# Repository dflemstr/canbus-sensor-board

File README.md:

# canbus sensor board

A simple board optimized for handling I²C-connected sensors and communicate the status over CAN bus.

This repo contains both the PCB design files, and Rust-based firmware.

To flash and run the firmware:

  * Install Rust.  Using [rustup](https://rustup.rs/) is very strongly encouraged as it automates
    installation of cross compilation files and such.
  * Install `probe-rs`, a CLI for connecting to debug probes, with `cargo install probe-rs`.
  * Install `flip-link`, a meta-linker that puts the stack at the end of embedded memory, using
    `cargo install flip-link`.
  * Optionally update the `DEFAULT_CAN_ID` variable in `src/config.rs` if you want to change the CAN
    bus ID of the board without having to send it a command later.

Flash using a debug probe (easiest):

  * Connect the PCB to your computer using a SWD-based debug probe, for example a ST-Link v2 clone
    can be found super cheaply online, usually around $3 USD.  You can either solder wires to the
    provided pads (see PCB design files for pin assignments) or else use a TagConnect TC2030-NL
    cable, which has pogo pins matching the pads on the board, and can be bought with adapter wires
    that are compatible with an ST-Link module.
  * Run `cargo flash --release --chip STM32F103C8 --connect-under-reset` to flash to the board **or**
    run `cargo run` to flash the firmware using a debug build, start it, and stream debug logs to the
    terminal using the defmt RTT protocol. (You can of course also do any combination, e.g.
    `cargo run --release` etc)

Flash using CAN bus (more tricky perhaps):

  * Install [`can-prog`](https://github.com/marcinbor85/can-Prog), see the link for additional
    details.
  * Connect the PCB to a CAN bus.
  * Using some wires, first short the 3.3V and BOOT pads, and while still shorting the pads, also
    short the ~RST and GND pads.  This should put the board in DFU mode.
  * Build the firmware in release mode with `cargo build --release`
  * Convert the generated ELF file to a raw `.bin` file with:
    ```
    arm-none-eabi-objcopy -O binary target/thumbv7m-none-eabi/release/canbus-sensor-board image.bin
    ```

  * Run the command `canprog -f bin stm32 write image.bin -a 0x08000000` or similar. You might need
    to run `canprog stm32 erase` and such depending on the state of the firmware.

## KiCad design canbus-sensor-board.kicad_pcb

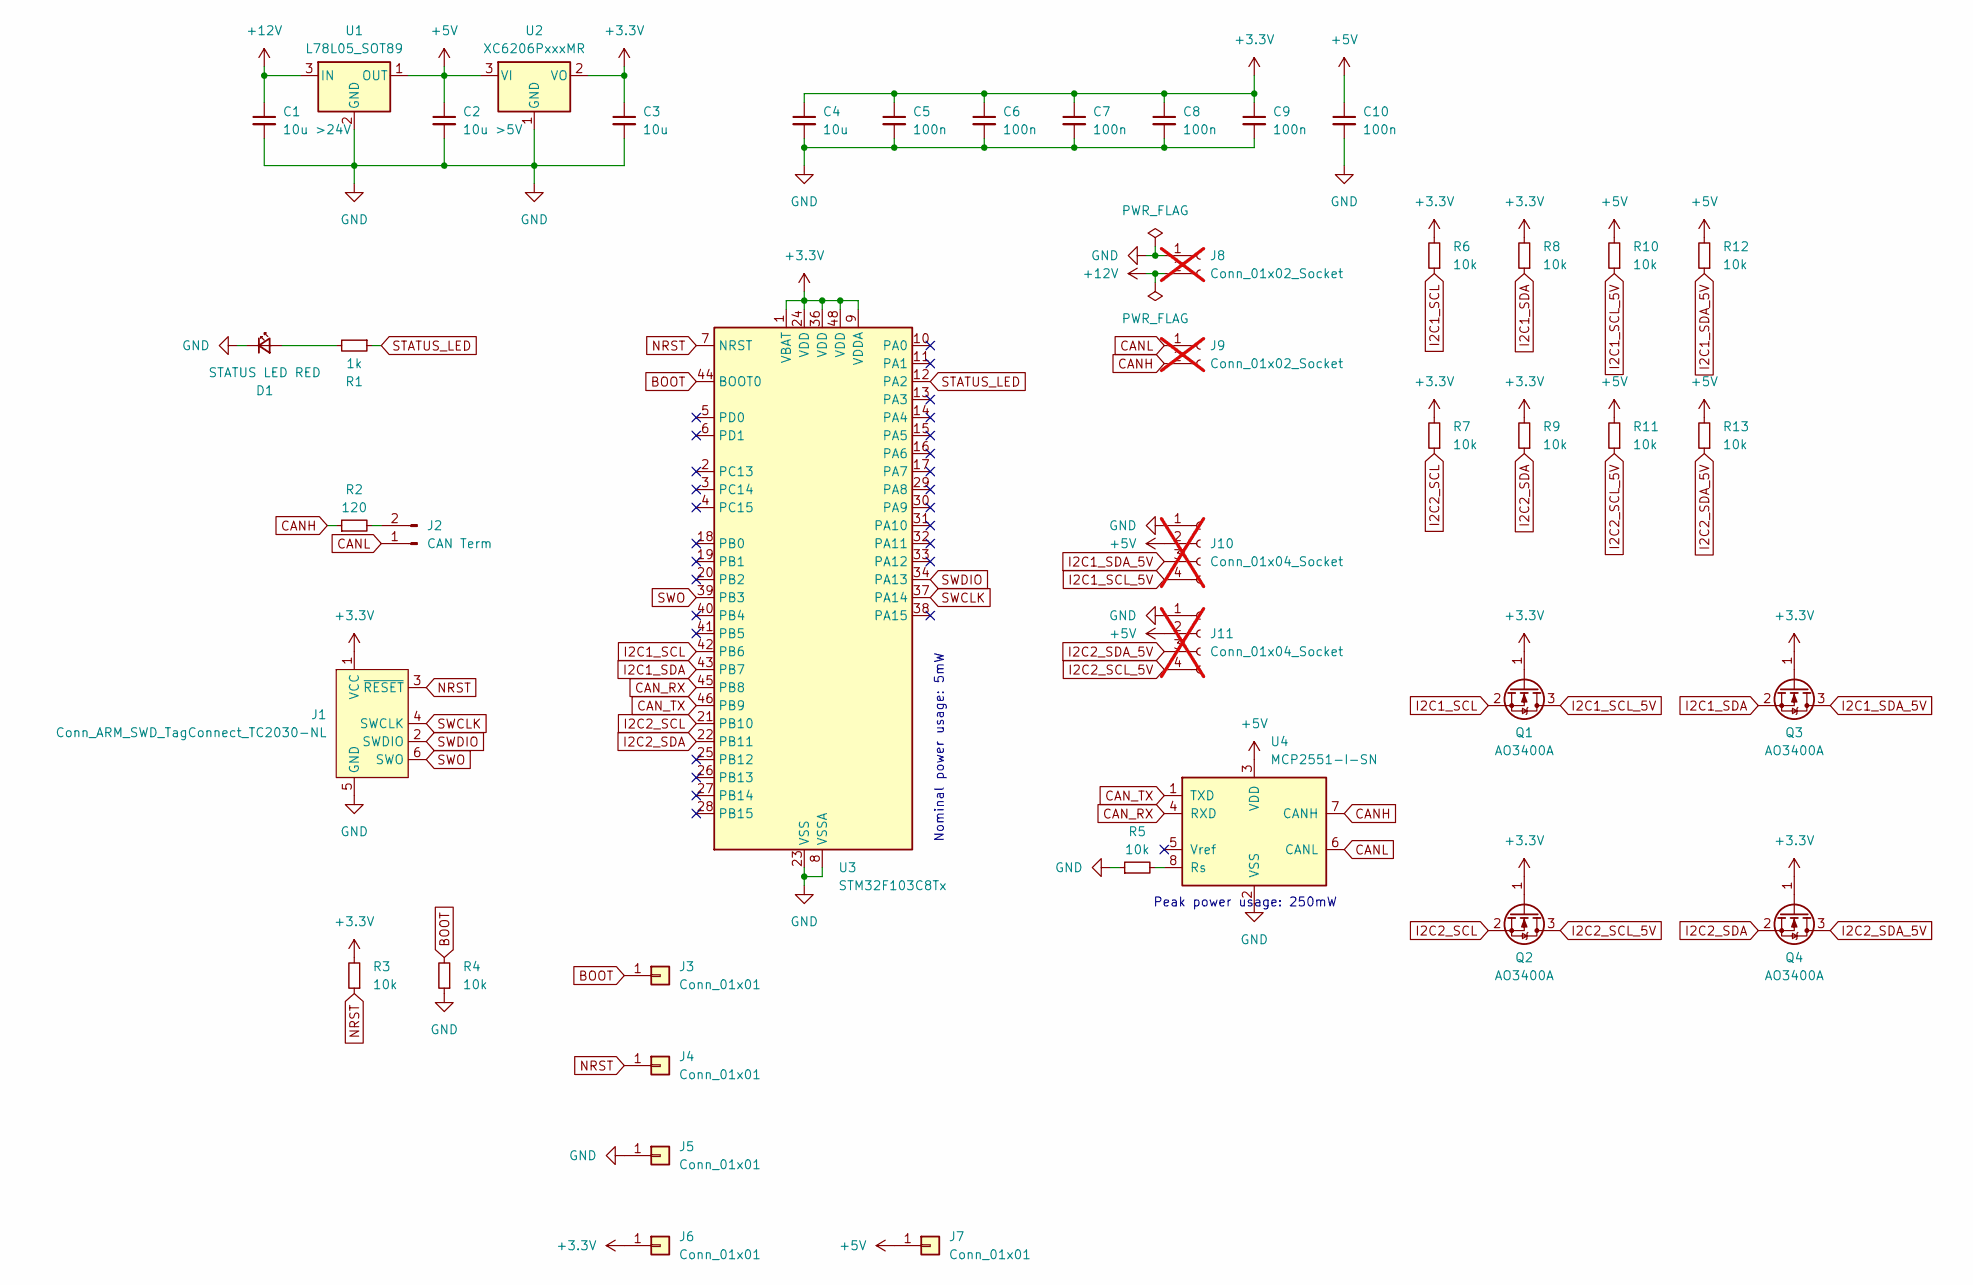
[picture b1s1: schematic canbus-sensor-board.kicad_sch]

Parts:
C1: 10u >24V; C_0805_2012Metric; MPN C440198
C2: 10u >5V; C_0603_1608Metric; MPN C19702
C3, C4: 10u; C_0402_1005Metric; MPN C15525
C5, C6, C7, C8, C9, C10: 100n; C_0402_1005Metric; MPN C1525
D1: STATUS LED RED; LED_0603_1608Metric; MPN C2286
J1: Conn_ARM_SWD_TagConnect_TC2030-NL; Tag-Connect_TC2030-IDC-NL_2x03_P1.27mm_Vertical
J2: CAN Term; SolderJumper-2_P1.3mm_Open_Pad1.0x1.5mm
J3, J4, J5, J6, J7: Conn_01x01; TestPoint_Pad_D1.0mm
J8, J9: Conn_01x02_Socket; PinHeader_1x02_P2.00mm_Vertical; not fitted
J10, J11: Conn_01x04_Socket; PinHeader_1x04_P2.00mm_Vertical; not fitted
Q1, Q2, Q3, Q4: AO3400A; SOT-23; MPN C20917
R1: 1k; R_0402_1005Metric; MPN C11702
R2: 120; R_0402_1005Metric; MPN C25079
R3, R4, R5, R6, R7, R8, R9, R10, R11, R12, R13: 10k; R_0402_1005Metric; MPN C25744
U1: L78L05_SOT89; SOT-89-3; MPN C71136
U2: XC6206PxxxMR; SOT-23-3; MPN C5446
U3: STM32F103C8Tx; LQFP-48_7x7mm_P0.5mm; MPN C8734
U4: MCP2551-I-SN; SOIC-8_3.9x4.9mm_P1.27mm; MPN C49558

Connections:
+3.3V: C3.1, C4.1, C5.1, C6.1, C7.1, C8.1, C9.1, J1.1 (VCC), J6.1, Q1.1 (G), Q2.1 (G), Q3.1 (G), Q4.1 (G), R3.2, R6.2, R7.2, R8.2, R9.2, U2.2 (VO), U3.1 (VBAT), U3.9 (VDDA), U3.24 (VDD), U3.36 (VDD), U3.48 (VDD)
+5V: C2.1, C10.1, J7.1, J10.2, J11.2, R10.2, R11.2, R12.2, R13.2, U1.1 (OUT), U2.3 (VI), U4.3 (VDD)
+12V: C1.1, J8.2, U1.3 (IN)
BOOT: J3.1, R4.2, U3.44 (BOOT0)
CANH: J9.2, R2.1, U4.7 (CANH)
CANL: J2.1, J9.1, U4.6 (CANL)
CAN_RX: U3.45 (PB8), U4.4 (RXD)
CAN_TX: U3.46 (PB9), U4.1 (TXD)
GND: C1.2, C2.2, C3.2, C4.2, C5.2, C6.2, C7.2, C8.2, C9.2, C10.2, D1.1 (K), J1.5 (GND), J5.1, J8.1, J10.1, J11.1, R4.1, R5.1, U1.2 (GND), U2.1 (GND), U3.8 (VSSA), U3.23 (VSS), U3.35 (VSS), U3.47 (VSS), U4.2 (VSS)
I2C1_SCL: Q1.2 (S), R6.1, U3.42 (PB6)
I2C1_SCL_5V: J10.4, Q1.3 (D), R10.1
I2C1_SDA: Q3.2 (S), R8.1, U3.43 (PB7)
I2C1_SDA_5V: J10.3, Q3.3 (D), R12.1
I2C2_SCL: Q2.2 (S), R7.1, U3.21 (PB10)
I2C2_SCL_5V: J11.4, Q2.3 (D), R11.1
I2C2_SDA: Q4.2 (S), R9.1, U3.22 (PB11)
I2C2_SDA_5V: J11.3, Q4.3 (D), R13.1
NRST: J1.3 (~RESET), J4.1, R3.1, U3.7 (NRST)
unnamed: D1.2 (A), R1.2
unnamed: J2.2, R2.2
unnamed: R5.2, U4.8 (Rs)
STATUS_LED: R1.1, U3.12 (PA2)
SWCLK: J1.4 (SWCLK), U3.37 (PA14)
SWDIO: J1.2 (SWDIO), U3.34 (PA13)
SWO: J1.6 (SWO), U3.39 (PB3)

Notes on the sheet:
Nominal power usage: 5mW
Peak power usage: 250mW

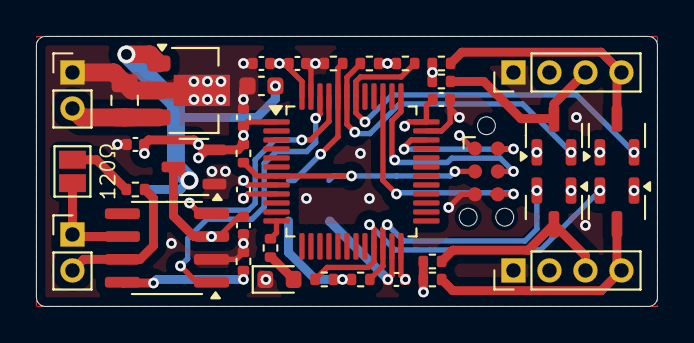
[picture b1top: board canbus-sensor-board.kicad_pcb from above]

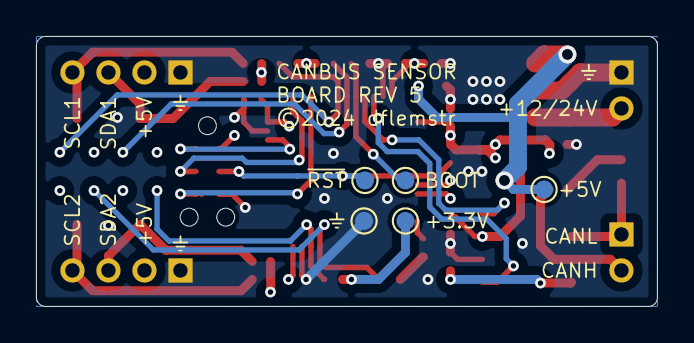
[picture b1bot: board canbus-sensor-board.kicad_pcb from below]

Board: 4 copper layers, 34.5 x 15.0 mm, 43 parts (5 on the bottom side), 25 nets.

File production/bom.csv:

Designator,Footprint,Quantity,Value,LCSC Part #
C1,0805,1,10u >24V,C440198
"C10, C5, C6, C7, C8, C9",0402,6,100n,C1525
C2,0603,1,10u >5V,C19702
"C3, C4",0402,2,10u,C15525
D1,0603,1,STATUS LED RED,C2286
"J10, J11",PinHeader_1x04_P2.00mm_Vertical,2,Conn_01x04_Socket,
J2,SolderJumper-2_P1.3mm_Open_Pad1.0x1.5mm,1,CAN Term,
"J3, J4, J5, J6, J7",TestPoint_Pad_D1.0mm,5,Conn_01x01,
"J8, J9",PinHeader_1x02_P2.00mm_Vertical,2,Conn_01x02_Socket,
"Q1, Q2, Q3, Q4",SOT-23,4,AO3400A,C20917
R1,0402,1,1k,C11702
"R10, R11, R12, R13, R3, R4, R5, R6, R7, R8, R9",0402,11,10k,C25744
R2,0402,1,120,C25079
U1,SOT-89-3,1,L78L05_SOT89,C71136
U2,SOT-23-3,1,XC6206PxxxMR,C5446
U3,LQFP-48_7x7mm_P0.5mm,1,STM32F103C8Tx,C8734
U4,SOIC-8_3.9x4.9mm_P1.27mm,1,MCP2551-I-SN,C49558

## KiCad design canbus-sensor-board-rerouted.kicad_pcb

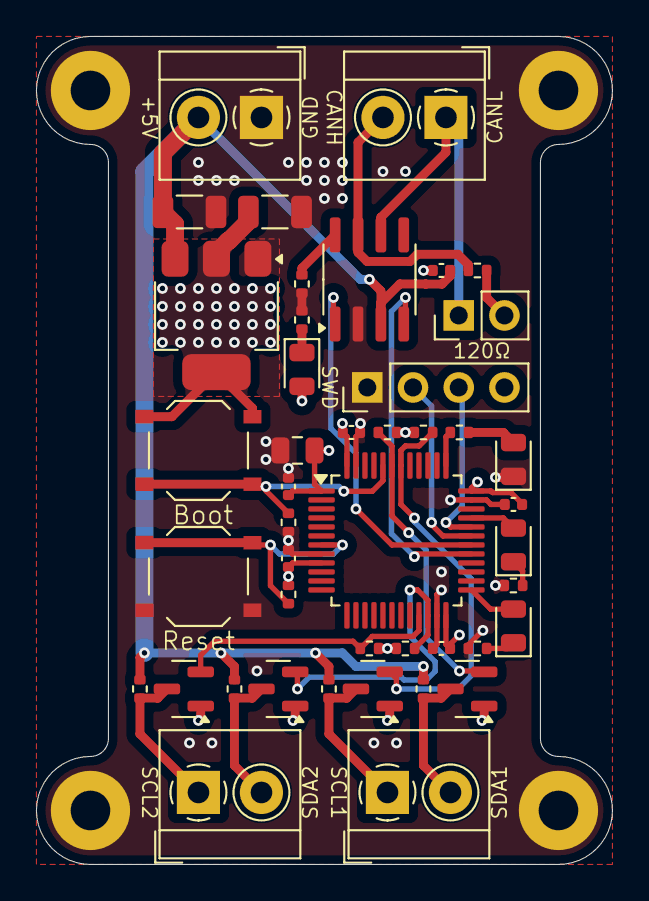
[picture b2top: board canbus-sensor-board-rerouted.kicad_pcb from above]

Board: 4 copper layers, 32.0 x 46.0 mm, 48 parts (0 on the bottom side), 28 nets.

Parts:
C1, C2, C3, C5, C8, C9: 100n; C_0402_1005Metric
C4: 10u; C_0805_2012Metric
C6, C7: 22u; C_1206_3216Metric
D1: Power (GREEN); LED_0805_2012Metric
D2: Debug LED 1 RED; LED_0805_2012Metric
D3: Debug LED 3 GREEN; LED_0805_2012Metric
D5: Debug LED 2 YELLOW; LED_0805_2012Metric
H1, H2, H3, H4: MountingHole_Pad; MountingHole_2.2mm_M2_Pad
J1: CAN IO; TerminalBlock_4Ucon_1x02_P3.50mm_Horizontal
J2: CAN Term; PinHeader_1x02_P2.54mm_Vertical
J3: POWER IN; TerminalBlock_4Ucon_1x02_P3.50mm_Horizontal
J4: Debug; PinHeader_1x04_P2.54mm_Vertical
J5: I2C2 IO; TerminalBlock_4Ucon_1x02_P3.50mm_Horizontal
J6: I2C1 IO; TerminalBlock_4Ucon_1x02_P3.50mm_Horizontal
Q1, Q2, Q3, Q4: 2N7002; SOT-23
R1: 120; R_0402_1005Metric
R2, R3, R4, R6, R7, R8, R9, R12, R14, R15, R16: 10k; R_0402_1005Metric
R5, R10, R11, R13: 1k; R_0402_1005Metric
SW1: Reset; SW_Push_1P1T_XKB_TS-1187A
SW2: Boot; SW_Push_1P1T_XKB_TS-1187A
U1: MCP2551-I-SN; SOIC-8_3.9x4.9mm_P1.27mm
U3: AMS1117-3.3; SOT-223-3_TabPin2
U4: STM32F103C8Tx; LQFP-48_7x7mm_P0.5mm

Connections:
+3.3V: C1.1, C2.1, C3.1, C4.1, C7.1, C8.1, C9.1, D1.2 (A), J4.4, Q1.1 (G), Q2.1 (G), Q3.1 (G), Q4.1 (G), R3.1, R6.2, R7.2, R8.2, R9.2, SW2.1 (A), U3.2 (VO), U4.1 (VBAT), U4.9 (VDDA), U4.24 (VDD), U4.36 (VDD), U4.48 (VDD)
+5V: C5.1, C6.1, J3.2, R12.2, R14.2, R15.2, R16.2, U1.3 (VDD), U3.3 (VI)
BOOT: R4.2, SW2.2 (B), U4.44 (BOOT0)
CANH: J1.2, R1.1, U1.7 (CANH)
CANL: J1.1, J2.1, U1.6 (CANL)
CAN_RX: U1.4 (RXD), U4.29 (PA8)
CAN_TX: U1.1 (TXD), U4.30 (PA9)
DEBUG_LED1: R10.1, U4.37 (PA14)
DEBUG_LED2: D5.2 (A), U4.33 (PA12)
DEBUG_LED3: D3.2 (A), U4.25 (PB12)
GND: C1.2, C2.2, C3.2, C4.2, C5.2, C6.2, C7.2, C8.2, C9.2, D2.1 (K), H1.1, H2.1, H3.1, H4.1, J3.1, J4.1, R2.1, R4.1, R5.1, R11.2, R13.2, SW1.1 (A), U1.2 (VSS), U3.1 (GND), U4.8 (VSSA), U4.23 (VSS), U4.35 (VSS), U4.47 (VSS)
I2C1_SCL: Q1.2 (S), R6.1, U4.42 (PB6)
I2C1_SCL_5V: J6.1, Q1.3 (D), R12.1
I2C1_SDA: Q2.2 (S), R7.1, U4.43 (PB7)
I2C1_SDA_5V: J6.2, Q2.3 (D), R14.1
I2C2_SCL: Q3.2 (S), R8.1, U4.21 (PB10)
I2C2_SCL_5V: J5.1, Q3.3 (D), R15.1
I2C2_SDA: Q4.2 (S), R9.1, U4.22 (PB11)
I2C2_SDA_5V: J5.2, Q4.3 (D), R16.1
NRST: R3.2, SW1.2 (B), U4.7 (NRST)
unnamed: D1.1 (K), R5.2
unnamed: D2.2 (A), R10.2
unnamed: D3.1 (K), R11.1
unnamed: D5.1 (K), R13.1
unnamed: J2.2, R1.2
unnamed: R2.2, U1.8 (Rs)
SYS_SWCLK: J4.3, U4.32 (PA11)
SYS_SWDIO: J4.2, U4.31 (PA10)

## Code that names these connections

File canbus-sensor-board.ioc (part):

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Mcu.Name=STM32F103C(8-B)Tx
Mcu.Package=LQFP48
Mcu.UserName=STM32F103C8Tx
PA12.Signal=GPIO_Output
PA13.Mode=Trace_Asynchronous_SW
PA13.Signal=SYS_JTMS-SWDIO
PA14.Mode=Trace_Asynchronous_SW
PA14.Signal=SYS_JTCK-SWCLK
PA15.Signal=GPIO_Output
PB10.Mode=I2C
PB10.Signal=I2C2_SCL
PB11.Mode=I2C
PB11.Signal=I2C2_SDA
PB12.Signal=GPIO_Output
PB3.Mode=Trace_Asynchronous_SW
PB3.Signal=SYS_JTDO-TRACESWO
PB6.Mode=I2C
PB6.Signal=I2C1_SCL
PB7.Mode=I2C
PB7.Signal=I2C1_SDA
PB8.Mode=CAN_Activate
PB8.Signal=CAN_RX
PB9.Mode=CAN_Activate
PB9.Signal=CAN_TX
board=custom

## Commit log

2024-05-04 Initial PCB design rev 1
2024-05-13 Add rerouted PCB (possible rev 2)
2024-05-13 Update board to rev 3 (we do not talk about rev 2)
2024-05-13 Slightly tweak some via positions
2024-05-13 Add README and basic firmware skeleton
2024-05-13 Add hint about changing default CAN id
2024-05-13 Actually use the flip-link linker
2024-05-13 Store CAN ID in a more reasonable flash location
2024-05-14 Switch to MOSFETs with lower Vgs thresholds
2024-05-14 Upgrade deps
2024-05-14 Fix some broken tracks
2024-05-15 Add somewhat complete firmware impl
2024-05-15 Huge refactor of firmware code into modules
2024-05-15 Make I2C bitrate more clearly configurable
2024-05-22 Tweak firmware so it works on the actual device :)
2024-05-22 Further tweak rev4 of the board
2024-05-23 Make i2c timeouts configurable
2024-05-24 Remove red LED
2024-05-24 Increase 12-24V cap size so it actually handles that voltage range
2024-05-24 Also make 5V cap larger to have more error margin
2024-05-30 Update firmware for rev 4 and add watchdog
2024-05-30 Use a render from the latest design
2024-05-30 Increase timer resolution and use better-compressed defmt strings
2024-05-30 Small documentation updates
2024-06-03 Misc logging fixes
2024-06-26 Store config vars in dedicated linker section and make them re-writable
2024-06-28 Store each config value in its own flash sector

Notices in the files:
canbus-sensor-board.kicad_pcb:
©2024 dflemstr
